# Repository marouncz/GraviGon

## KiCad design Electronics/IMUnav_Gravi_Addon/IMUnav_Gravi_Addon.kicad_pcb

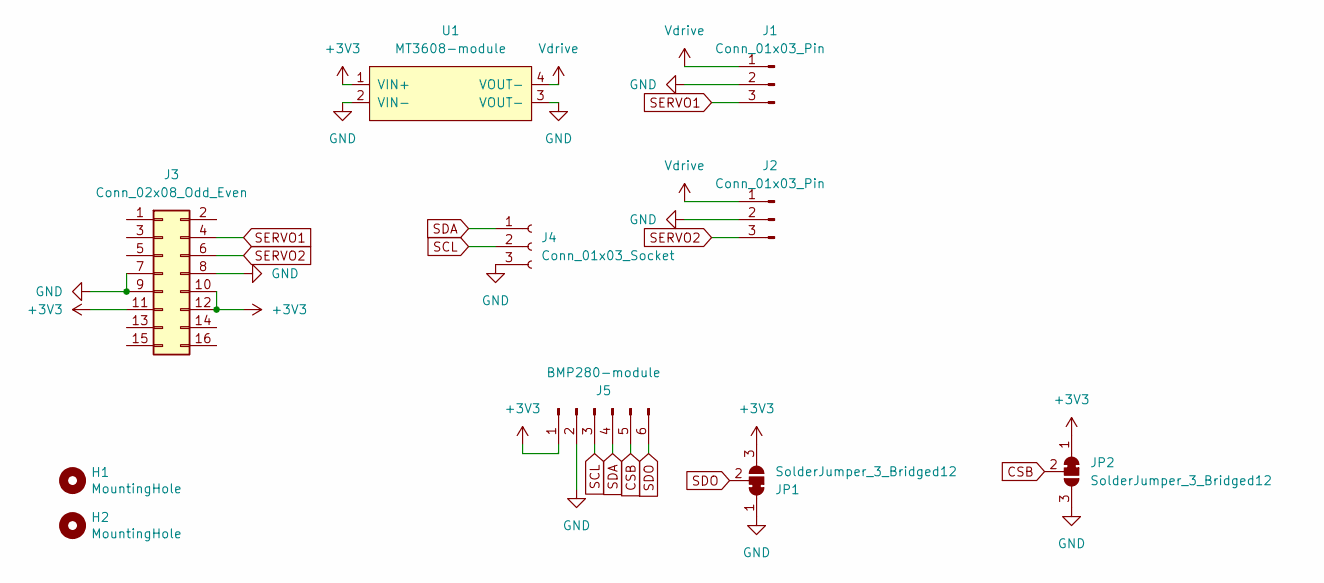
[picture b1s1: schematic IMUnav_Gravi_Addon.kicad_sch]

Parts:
H1, H2: MountingHole; MountingHole_3.2mm_M3
J1, J2: Conn_01x03_Pin; PinHeader_1x03_P2.54mm_Vertical
J3: Conn_02x08_Odd_Even; PinSocket_2x08_P2.00mm_Vertical
J4: Conn_01x03_Socket; PinSocket_1x03_P2.54mm_Vertical
J5: BMP280-module; PinSocket_1x06_P2.54mm_Vertical
JP1, JP2: SolderJumper_3_Bridged12; SolderJumper-3_P1.3mm_Bridged12_RoundedPad1.0x1.5mm_NumberL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
U1: MT3608-module; hw-045

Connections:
+3V3: J3.10, J3.11, J3.12, J5.1, JP1.3 (B), JP2.1 (A), U1.1 (VIN+)
CSB: J5.5, JP2.2 (C)
GND: J1.2, J2.2, J3.7, J3.8, J3.9, J4.3, J5.2, JP1.1 (A), JP2.3 (B), U1.2 (VIN-), U1.3 (VOUT-)
SCL: J4.2, J5.3
SDA: J4.1, J5.4
SDO: J5.6, JP1.2 (C)
SERVO1: J1.3, J3.4
SERVO2: J2.3, J3.6
Vdrive: J1.1, J2.1, U1.4 (VOUT-)

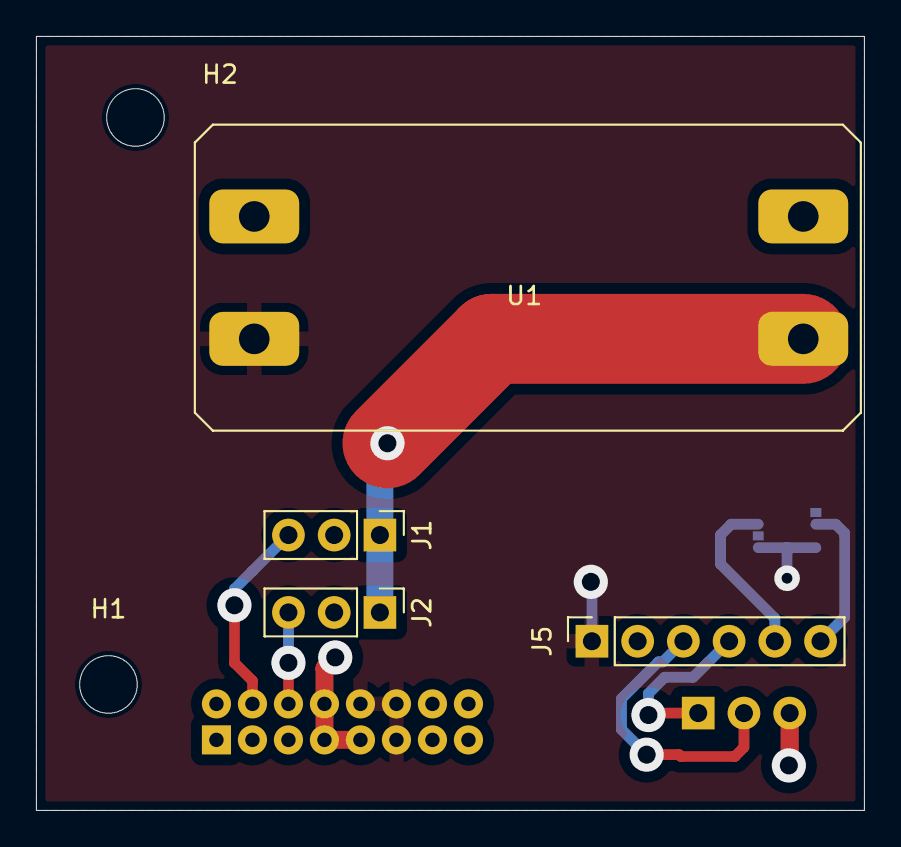
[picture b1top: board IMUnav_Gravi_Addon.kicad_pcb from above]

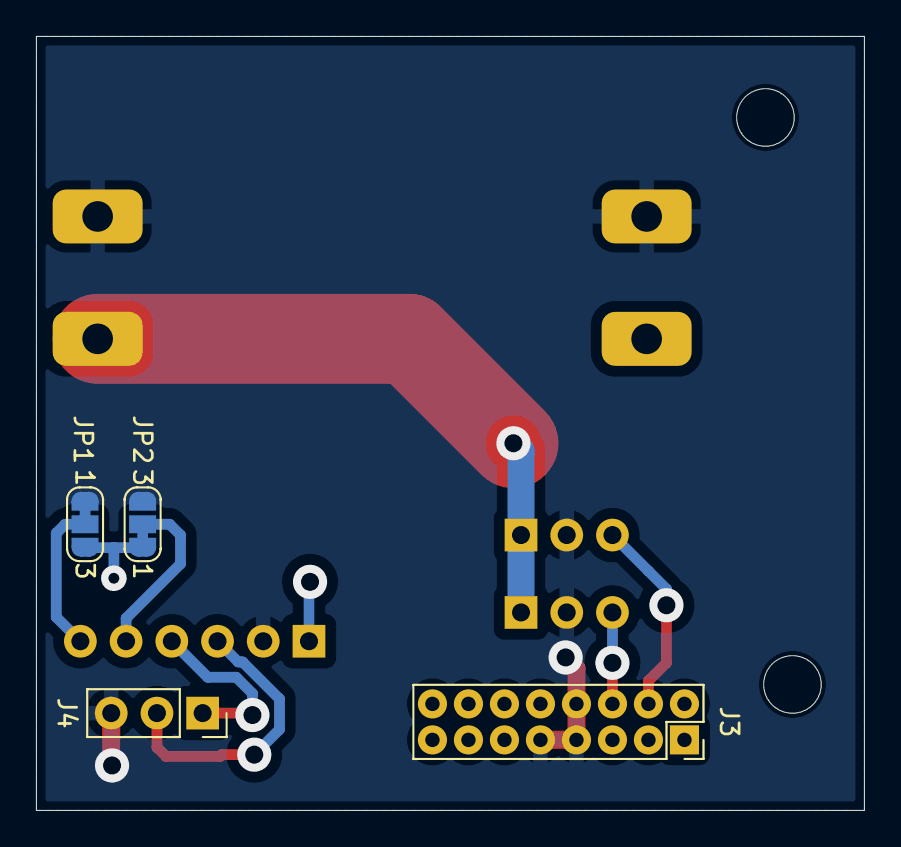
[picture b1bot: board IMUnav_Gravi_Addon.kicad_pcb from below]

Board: 2 copper layers, 46.0 x 43.0 mm, 10 parts (4 on the bottom side), 9 nets.

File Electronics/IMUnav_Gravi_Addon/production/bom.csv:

Designator,Footprint,Quantity,Value,LCSC Part #
"J1, J2",PinHeader_1x03_P2.54mm_Vertical,2,Conn_01x03_Pin,
J3,PinSocket_2x08_P2.00mm_Vertical,1,Conn_02x08_Odd_Even,
J4,PinSocket_1x03_P2.54mm_Vertical,1,Conn_01x03_Socket,
J5,PinSocket_1x06_P2.54mm_Vertical,1,BMP280-module,
U1,hw-045,1,MT3608-module,

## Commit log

2025-02-20 addon pcb kicad project
2025-02-20 addon pcb, added 3d models
2025-02-21 addon pcb routing
2025-02-26 nákupní seznam
2025-03-02 update for manufacturability with npth vias
2025-03-24 initial software rework
2025-03-26 freefall detection
2025-04-13 pressure, new logger
2025-04-13 fixed fatfs problems, logging struct update
2025-04-13 logger and binary decoder
2025-04-13 filesystem sync to save data when power outage
2025-04-13 logging magnetometer
2025-04-14 holedná test fall
2025-04-14 holedná fail
2025-04-14 imunav board
2025-04-14 mechanical
2025-04-23 failsafe button, bilovice test
2025-05-02 diagramy
2025-05-04 3D model update
